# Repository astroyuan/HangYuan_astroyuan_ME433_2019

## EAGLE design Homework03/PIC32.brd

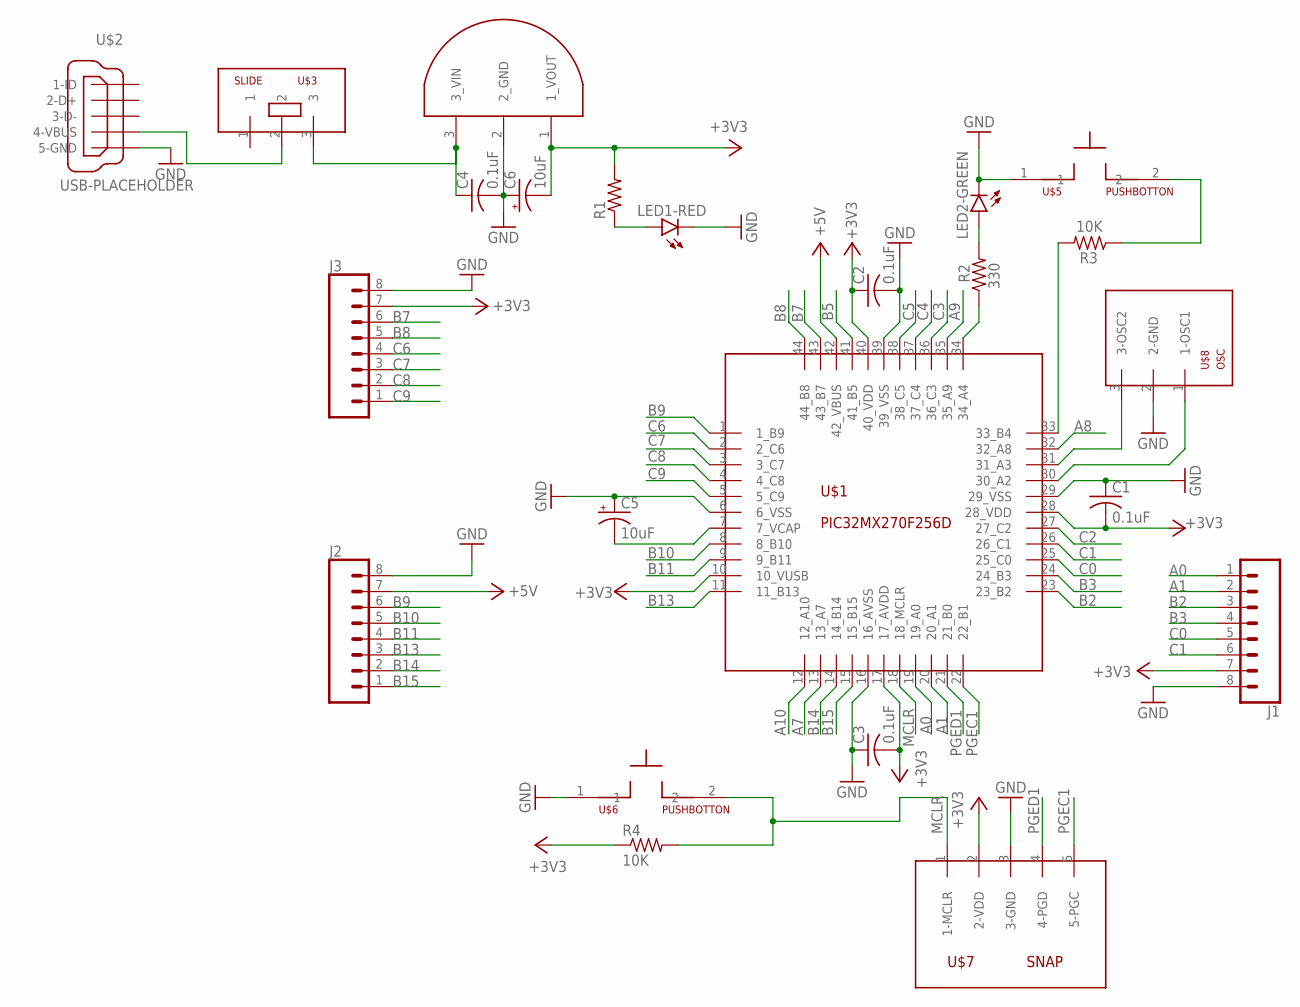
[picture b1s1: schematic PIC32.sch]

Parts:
C1, C2, C3, C4: 0.1uF; C025-025X050
C5, C6: 10uF; B45181B
J1, J2, J3: CONN_08"; 1X08
LED1-RED, LED2-GREEN: LED3MM
R1: R-US_0207/10; 0207/10
R2: 330; 0207/10
R3, R4: 10K; 0207/10
U$1: PIC32MX270F256D; TQFP44
U$2: USB-PLACEHOLDER; USB-B-MICRO-SMD_V04
U$3: SLIDE
U$4: L4931; TO92-
U$5, U$6: PUSHBOTTON
U$7: SNAP; 1X05
U$8: OSC

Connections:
+3V3: C1.2, C2.1, C3.2, C6.-, J1.7, J3.7, R1.2, R4.1, U$1.10 (10_VUSB), U$1.17 (17_AVDD), U$1.28 (28_VDD), U$1.40 (40_VDD), U$4.1 (1_VOUT), U$7.2 (2-VDD)
+5V: J2.7, U$1.42 (42_VBUS)
A0: J1.1, U$1.19 (19_A0)
A1: J1.2, U$1.20 (20_A1)
A7: U$1.13 (13_A7)
A8: U$1.32 (32_A8)
A9: U$1.35 (35_A9)
A10: U$1.12 (12_A10)
B2: J1.3, U$1.23 (23_B2)
B3: J1.4, U$1.24 (24_B3)
B5: U$1.41 (41_B5)
B7: J3.6, U$1.43 (43_B7)
B8: J3.5, U$1.44 (44_B8)
B9: J2.6, U$1.1 (1_B9)
B10: J2.5, U$1.8 (8_B10)
B11: J2.4, U$1.9 (9_B11)
B13: J2.3, U$1.11 (11_B13)
B14: J2.2, U$1.14 (14_B14)
B15: J2.1, U$1.15 (15_B15)
C0: J1.5, U$1.25 (25_C0)
C1: J1.6, U$1.26 (26_C1)
C2: U$1.27 (27_C2)
C3: U$1.36 (36_C3)
C4: U$1.37 (37_C4)
C5: U$1.38 (38_C5)
C6: J3.4, U$1.2 (2_C6)
C7: J3.3, U$1.3 (3_C7)
C8: J3.2, U$1.4 (4_C8)
C9: J3.1, U$1.5 (5_C9)
GND: C1.1, C2.2, C3.1, C4.2, C5.+, C6.+, J1.8, J2.8, J3.8, LED1-RED.K (C), LED2-GREEN.K (C), U$1.6 (6_VSS), U$1.16 (16_AVSS), U$1.29 (29_VSS), U$1.39 (39_VSS), U$2.VBUS1 (5-GND), U$4.2 (2_GND), U$5.1, U$6.1, U$7.3 (3-GND), U$8.2 (2-GND)
MCLR: R4.2, U$1.18 (18_MCLR), U$6.2, U$7.1 (1-MCLR)
unnamed: U$2.ID1 (4-VBUS), U$3.2
unnamed: C5.-, U$1.7 (7_VCAP)
unnamed: C4.1, U$3.3, U$4.3 (3_VIN)
unnamed: LED1-RED.A, R1.1
unnamed: U$1.31 (31_A3), U$8.3 (3-OSC2)
unnamed: U$1.30 (30_A2), U$8.1 (1-OSC1)
unnamed: R3.2, U$1.33 (33_B4)
unnamed: R3.1, U$5.2
unnamed: R2.1, U$1.34 (34_A4)
unnamed: LED2-GREEN.A, R2.2
PGEC1: U$1.22 (22_B1), U$7.5 (5-PGC)
PGED1: U$1.21 (21_B0), U$7.4 (4-PGD)

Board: 2 copper layers, 23 parts (0 on the bottom side), 34 nets, no tracks yet.

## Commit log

2019-04-03 first commit. clean project folder for HW1.
2019-04-04 update control code.
2019-04-04 update code.
2019-04-04 Add pics and video.
2019-04-07 Library building in progress.
2019-04-09 Library building done. Schematic pending.
2019-04-10 Schematic Done.
2019-04-10 PCB design in progress.
2019-04-16 update code part.
2019-04-16 Code part finished implementation. Pending debug.
2019-04-17 Fix typos.
2019-04-17 Prepare starting code for hw5
2019-04-18 Clean up hw4 and ready for test.
2019-04-18 Framework of hw5 ready. Pending implementation.
2019-04-21 1. Timer cannot use modulo to allow some delay tolerance. 2. Need conversion from int to double
2019-04-21 Fixed timer design. hw4 needs an oscilloscope to prove it. hw5 in progress.
2019-04-21 Add schematic diagrams.
2019-04-21 hw05 done.
2019-04-21 prepare files for hw6.
2019-04-23 Cannot get it initialized...................... pending
2019-04-23 hw06 done.
2019-04-23 hw07 in progress.
2019-04-24 hw07 done.
2019-04-25 hw08 in progress.
2019-04-26 hw08 done.
2019-04-30 prepare framework for hw09.
2019-05-01 hw09 done.
2019-05-05 Raw CDC code from Harmony.
2019-05-05 roughly done. But there is a strange bug...
2019-05-07 hw10 done.
2019-05-10 Bug fixed. Marked as done.
2019-05-10 hw11 done.
2019-05-10 Raw code from Harmony.
2019-05-10 Example code.
2019-05-10 hw12 done.
2019-05-20 hw13 done.
2019-05-23 prepare files.
2019-05-24 Add pics.
2019-06-12 In progress of final robot.
2019-06-13 In progress. Camera does not work yet.
2019-06-14 upload 15 and 16.
2019-06-14 add pictures.
